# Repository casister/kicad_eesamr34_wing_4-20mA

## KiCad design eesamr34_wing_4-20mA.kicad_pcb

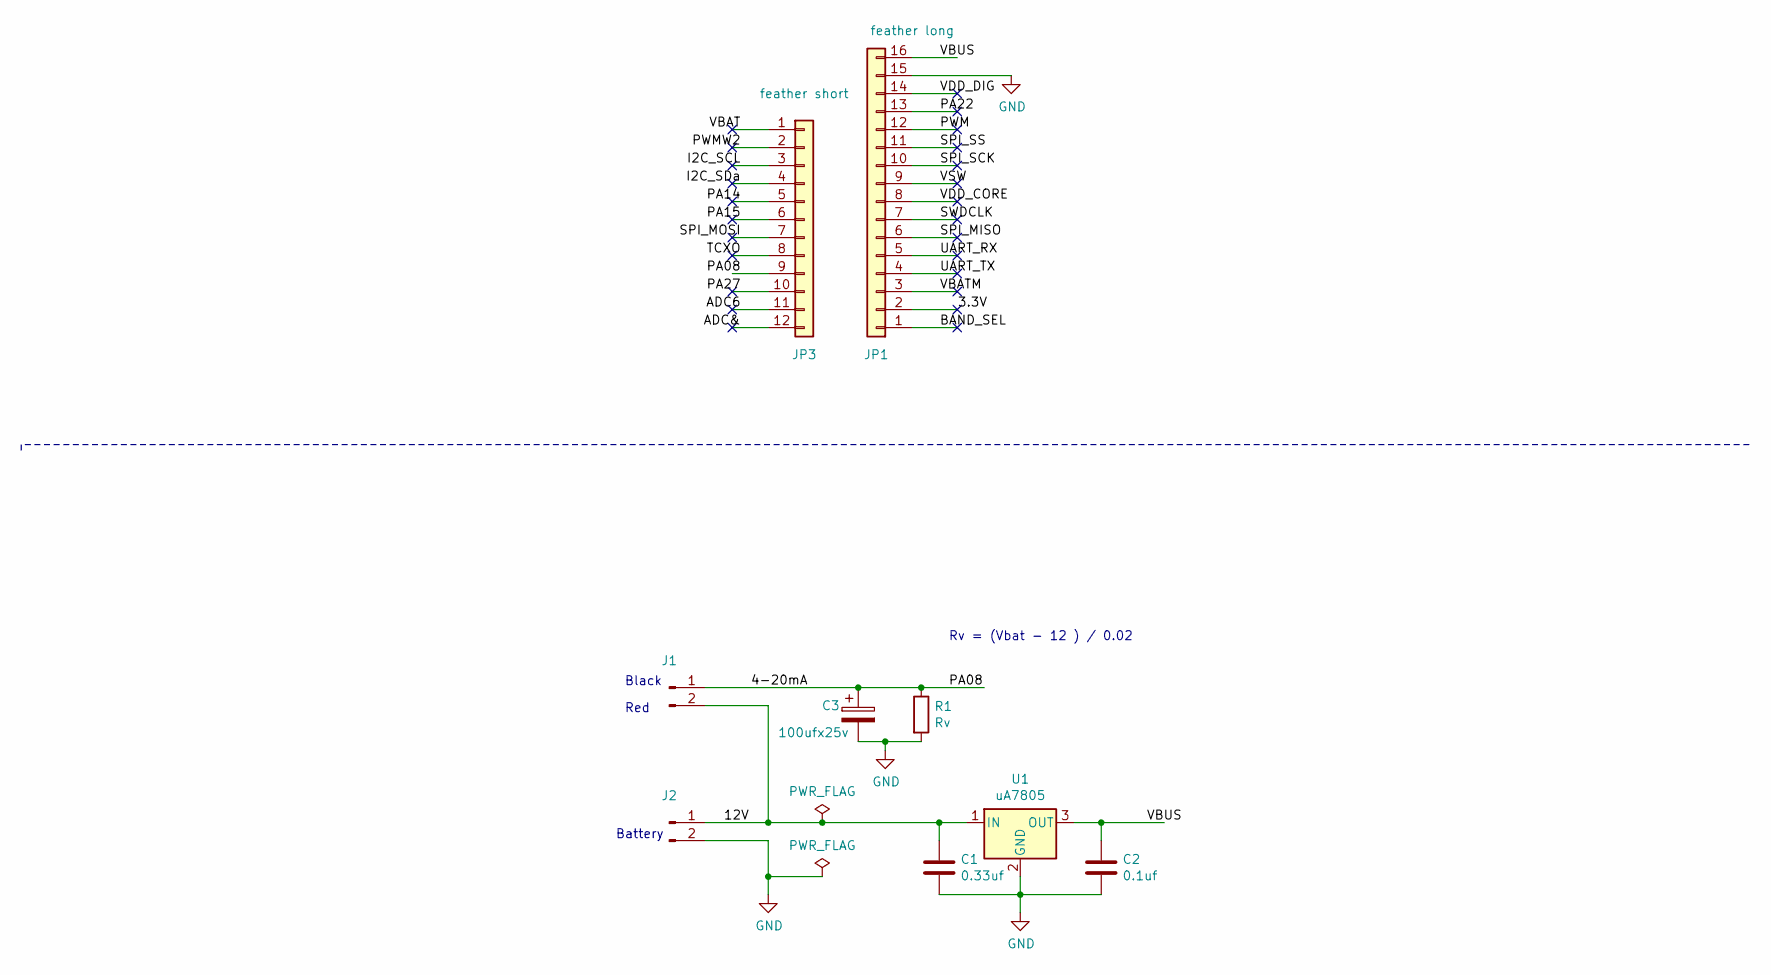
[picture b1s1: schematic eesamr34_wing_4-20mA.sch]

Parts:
C1: 0.33uf; C_Disc_D5.0mm_W2.5mm_P2.50mm
C2: 0.1uf; C_Disc_D5.0mm_W2.5mm_P2.50mm
C3: 100ufx25v; CP_Radial_D6.3mm_P2.50mm
J1, J2: Conn_01x02_Male; TerminalBlock_bornier-2_P5.08mm
JP1: feather long; PinHeader_1x16_P2.54mm_Vertical
JP3: feather short; PinHeader_1x12_P2.54mm_Vertical
R1: Rv; R_Axial_DIN0207_L6.3mm_D2.5mm_P7.62mm_Horizontal
U1: uA7805; TO-220-3_Vertical

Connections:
/3.3V: JP1.2
/4-20mA: C3.1, J1.1, JP3.9, R1.1
/12V: C1.1, J1.2, J2.1, U1.1 (IN)
/ADC6: JP3.11
/ADC&: JP3.12
/BAND_SEL: JP1.1
/I2C_SCL: JP3.3
/I2C_SDa: JP3.4
/PA14: JP3.5
/PA15: JP3.6
/PA22: JP1.13
/PA27: JP3.10
/PWM: JP1.12
/PWMW2: JP3.2
/SPI_MISO: JP1.6
/SPI_MOSI: JP3.7
/SPI_SCK: JP1.10
/SPI_SS: JP1.11
/SWDCLK: JP1.7
/TCXO: JP3.8
/UART_RX: JP1.5
/UART_TX: JP1.4
/VBAT: JP3.1
/VBATM: JP1.3
/VBUS: C2.1, JP1.16, U1.3 (OUT)
/VDD_CORE: JP1.8
/VDD_DIG: JP1.14
/VSW: JP1.9
GND: C1.2, C2.2, C3.2, J2.2, JP1.15, R1.2, U1.2 (GND)

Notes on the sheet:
Red
Black
Battery
Rv = (Vbat - 12 ) / 0.02

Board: 2 copper layers, 9 parts (2 on the bottom side), 4 nets, no tracks yet.

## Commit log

2020-10-13 First Version
